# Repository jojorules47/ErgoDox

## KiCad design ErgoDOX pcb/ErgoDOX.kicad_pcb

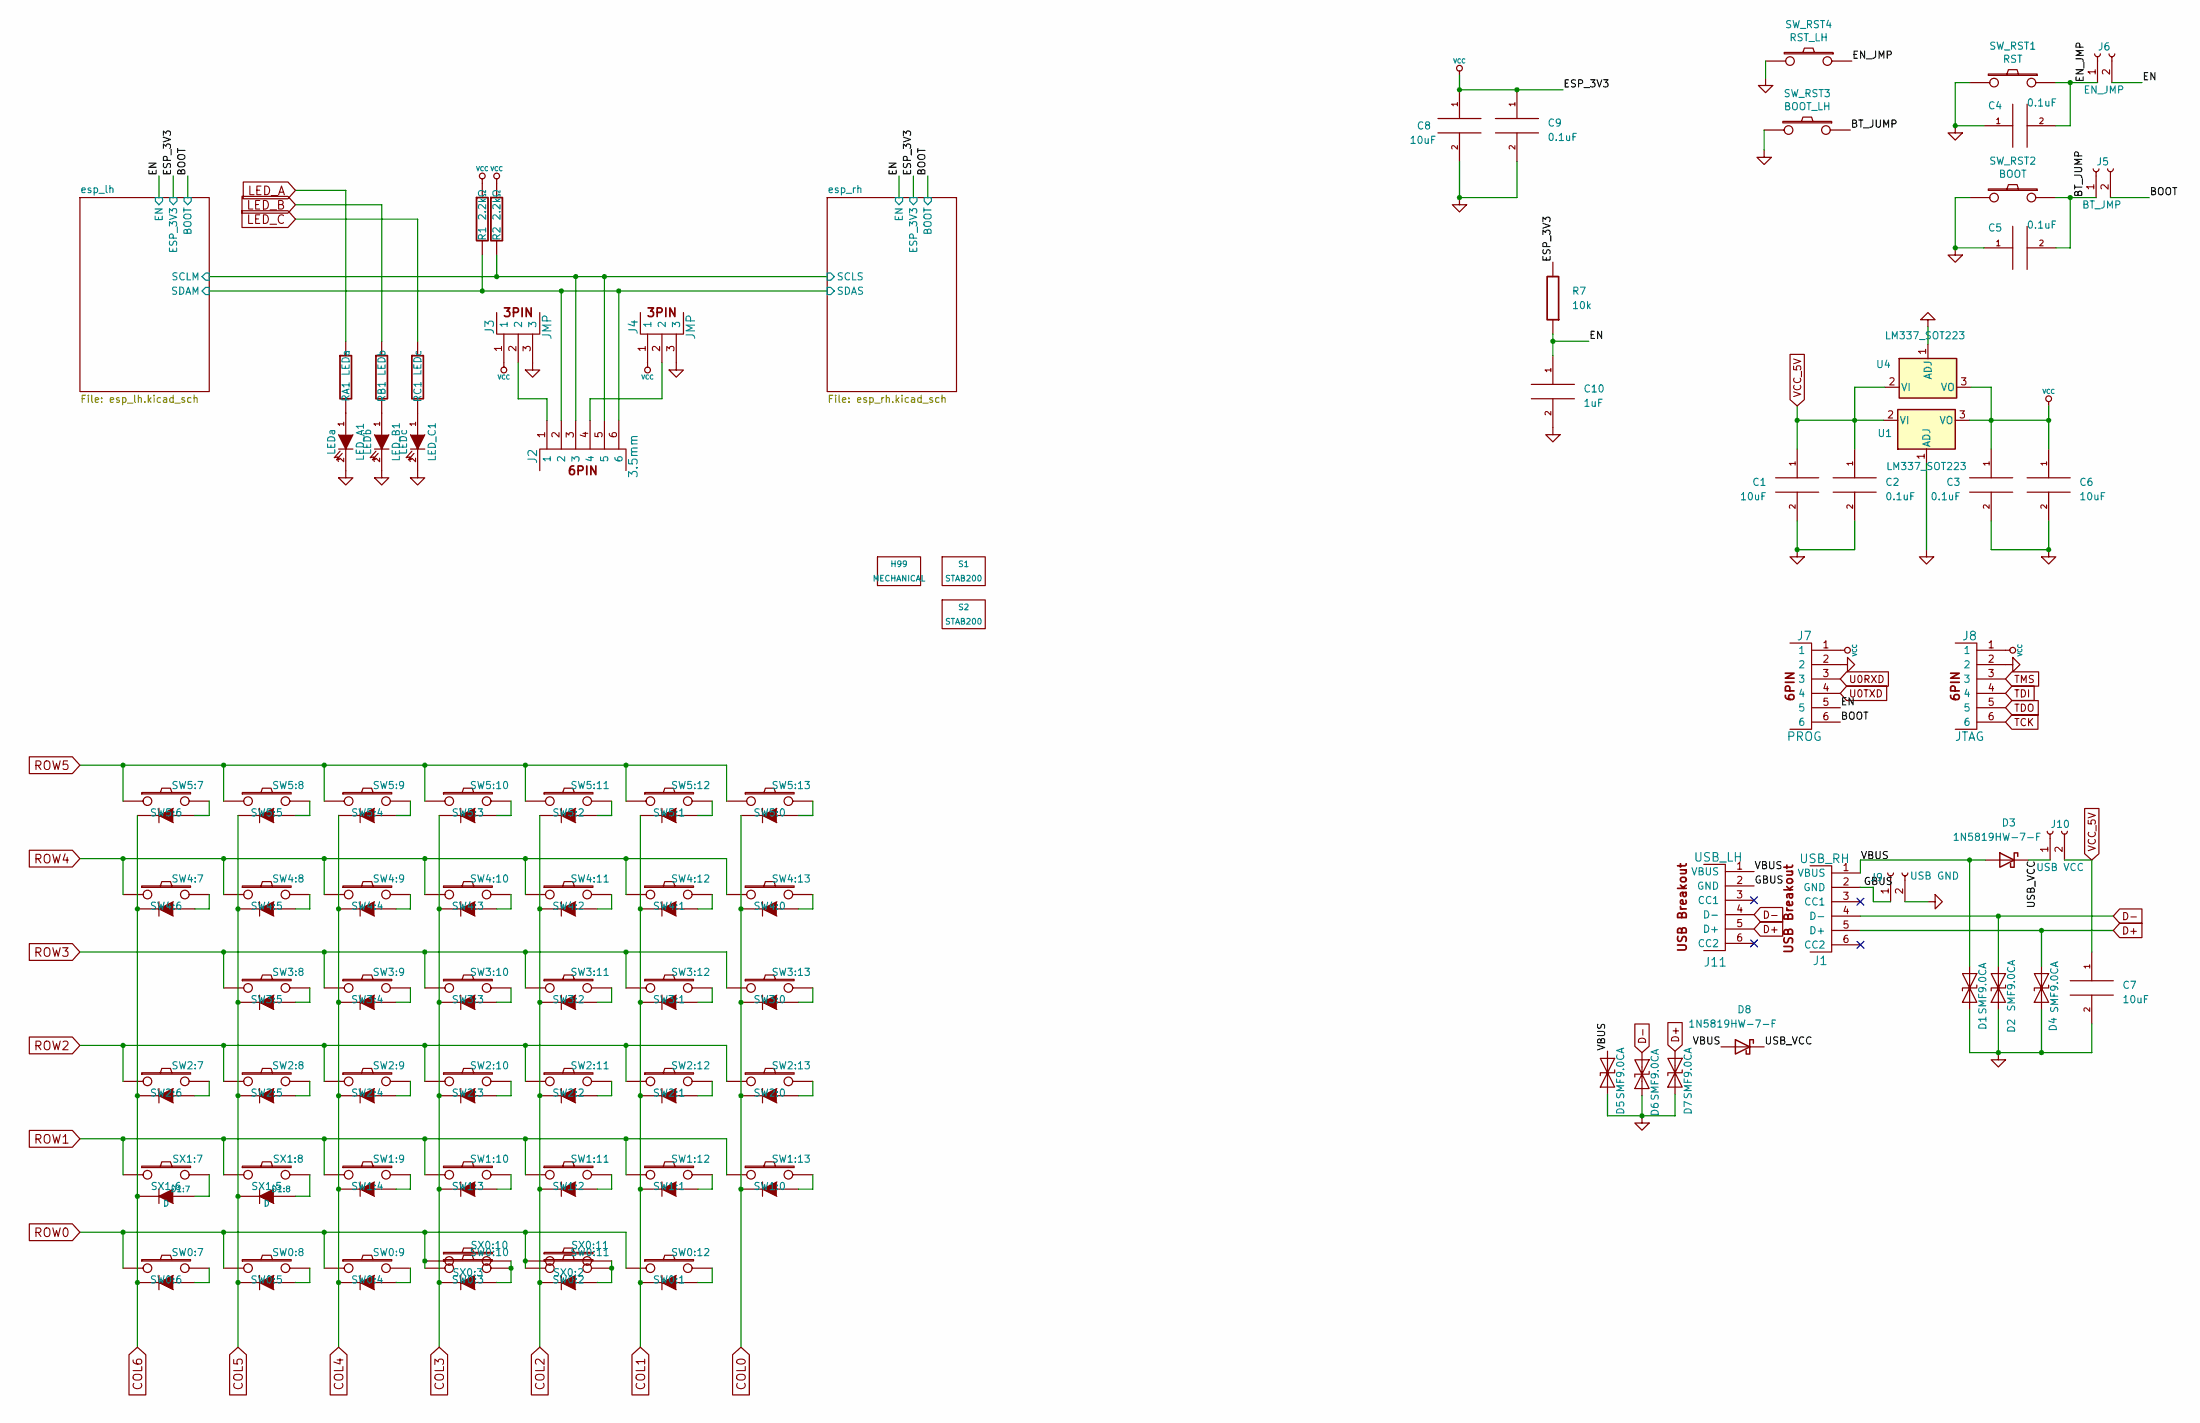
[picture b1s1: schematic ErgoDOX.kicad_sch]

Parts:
C1, C6, C7, C8: 10uF; C_Disc_D5.0mm_W2.5mm_P5.00mm
C2, C3, C4, C5, C9: 0.1uF; C_Disc_D5.0mm_W2.5mm_P5.00mm
C10: 1uF; C_Disc_D5.0mm_W2.5mm_P5.00mm
D1, D2, D4, D5, D6, D7: SMF9.0CA; D_SOD-123
D1:7, D1:8: D
D3, D8: 1N5819HW-7-F; D_SOD-123
H99: MECHANICAL
J1: USB_RH; SF USB-C Breakout
J2: 3.5mm
J3, J4: JMP
J5: BT_JMP; PinHeader_1x02_P2.54mm_Vertical
J6: EN_JMP; PinHeader_1x02_P2.54mm_Vertical
J7: PROG; PinHeader_1x06_P2.54mm_Vertical
J8: JTAG; PinHeader_1x06_P2.54mm_Vertical
J9: USB GND; PinHeader_1x02_P2.54mm_Vertical
J10: USB VCC; PinHeader_1x02_P2.54mm_Vertical
J11: USB_LH; SF USB-C Breakout
LED_A1: LEDa
LED_B1: LEDb
LED_C1: LEDc
R1, R2: 2.2kΩ; R_Axial_DIN0207_L6.3mm_D2.5mm_P7.62mm_Horizontal
R7: 10k; R_Axial_DIN0207_L6.3mm_D2.5mm_P7.62mm_Horizontal
RA1: LEDa; R_Axial_DIN0207_L6.3mm_D2.5mm_P7.62mm_Horizontal
RB1: LEDb; R_Axial_DIN0207_L6.3mm_D2.5mm_P7.62mm_Horizontal
RC1: LEDc; R_Axial_DIN0207_L6.3mm_D2.5mm_P7.62mm_Horizontal
S1, S2: STAB200
SW0:7: SW0:6
SW0:8: SW0:5
SW0:9: SW0:4
SW0:10: SW0:3
SW0:11: SW0:2
SW0:12: SW0:1
SW1:9: SW1:4
SW1:10: SW1:3
SW1:11: SW1:2
SW1:12: SW1:1
SW1:13: SW1:0
SW2:7: SW2:6
SW2:8: SW2:5
SW2:9: SW2:4
SW2:10: SW2:3
SW2:11: SW2:2
SW2:12: SW2:1
SW2:13: SW2:0
SW3:8: SW3:5
SW3:9: SW3:4
SW3:10: SW3:3
SW3:11: SW3:2
SW3:12: SW3:1
SW3:13: SW3:0
SW4:7: SW4:6
SW4:8: SW4:5
SW4:9: SW4:4
SW4:10: SW4:3
SW4:11: SW4:2
SW4:12: SW4:1
SW4:13: SW4:0
SW5:7: SW5:6
SW5:8: SW5:5
SW5:9: SW5:4
SW5:10: SW5:3
SW5:11: SW5:2
SW5:12: SW5:1
SW5:13: SW5:0
SW_RST1: RST; SW_SPST_B3U-1000P
SW_RST2: BOOT; SW_SPST_B3U-1000P
SW_RST3: BOOT_LH; SW_SPST_B3U-1000P
SW_RST4: RST_LH; SW_SPST_B3U-1000P
SX0:10: SX0:3
SX0:11: SX0:2
SX1:7: SX1:6
SX1:8: SX1:5
U1, U4: LM337_SOT223; SOT-223-3_TabPin2

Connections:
/BOOT: J5.2, J7.6; also elsewhere on the board
/BT_JUMP: C5.2, J5.1, SW_RST2.1, SW_RST3.1
/EN: C10.1, J6.2, J7.5, R7.1; also elsewhere on the board
/EN_JMP: C4.2, J6.1, SW_RST1.1, SW_RST4.1
/GBUS: J1.2 (GND), J9.1, J11.2 (GND)
/USB_VCC: D3.1 (K), D8.1 (K), J10.1
/VBUS: D1.2 (A2), D3.2 (A), D5.2 (A2), D8.2 (A), J1.1 (VBUS), J11.1 (VBUS)
COL0: SW1:13.4 (K), SW2:13.4 (K), SW3:13.4 (K), SW4:13.4 (K), SW5:13.4 (K); also elsewhere on the board
COL1: SW0:12.4 (K), SW1:12.4 (K), SW2:12.4 (K), SW3:12.4 (K), SW4:12.4 (K), SW5:12.4 (K); also elsewhere on the board
COL2: SW0:11.4 (K), SW1:11.4 (K), SW2:11.4 (K), SW3:11.4 (K), SW4:11.4 (K), SW5:11.4 (K); also elsewhere on the board
COL3: SW0:10.4 (K), SW1:10.4 (K), SW2:10.4 (K), SW3:10.4 (K), SW4:10.4 (K), SW5:10.4 (K); also elsewhere on the board
COL4: SW0:9.4 (K), SW1:9.4 (K), SW2:9.4 (K), SW3:9.4 (K), SW4:9.4 (K), SW5:9.4 (K); also elsewhere on the board
COL5: D1:8.2 (K), SW0:8.4 (K), SW2:8.4 (K), SW3:8.4 (K), SW4:8.4 (K), SW5:8.4 (K); also elsewhere on the board
COL6: D1:7.2 (K), SW0:7.4 (K), SW2:7.4 (K), SW4:7.4 (K), SW5:7.4 (K); also elsewhere on the board
D+: D4.2 (A2), D7.2 (A2), J1.5 (D+), J11.5 (D+); also elsewhere on the board
D-: D2.2 (A2), D6.2 (A2), J1.4 (D-), J11.4 (D-); also elsewhere on the board
GND: C1.2, C2.2, C3.2, C4.1, C5.1, C6.2, C7.2, C8.2, C9.2, C10.2, D1.1 (A1), D2.1 (A1), D4.1 (A1), D5.1 (A1), D6.1 (A1), D7.1 (A1), J3.3, J4.3, J7.2, J8.2, J9.2, LED_A1.2 (K), LED_B1.2 (K), LED_C1.2 (K), SW_RST1.2, SW_RST2.2, SW_RST3.2, SW_RST4.2, U1.1 (ADJ), U4.1 (ADJ); also elsewhere on the board
LED_A: RA1.1; also elsewhere on the board
LED_B: RB1.1; also elsewhere on the board
LED_C: RC1.1; also elsewhere on the board
unnamed: D1:7.1 (A), SX1:7.2
unnamed: D1:8.1 (A), SX1:8.2
unnamed: J2.4, J4.2
unnamed: J2.1, J3.2
unnamed: LED_A1.1 (A), RA1.2
unnamed: LED_B1.1 (A), RB1.2
unnamed: LED_C1.1 (A), RC1.2
unnamed: SW0:7.2, SW0:7.3 (A)
unnamed: SW0:8.2, SW0:8.3 (A)
unnamed: SW0:9.2, SW0:9.3 (A)
unnamed: SW0:10.2, SW0:10.3 (A), SX0:10.2
unnamed: SW0:11.2, SW0:11.3 (A), SX0:11.2
unnamed: SW0:12.2, SW0:12.3 (A)
unnamed: SW1:9.2, SW1:9.3 (A)
unnamed: SW1:10.2, SW1:10.3 (A)
unnamed: SW1:11.2, SW1:11.3 (A)
unnamed: SW1:12.2, SW1:12.3 (A)
unnamed: SW1:13.2, SW1:13.3 (A)
unnamed: SW2:7.2, SW2:7.3 (A)
unnamed: SW2:8.2, SW2:8.3 (A)
unnamed: SW2:9.2, SW2:9.3 (A)
unnamed: SW2:10.2, SW2:10.3 (A)
unnamed: SW2:11.2, SW2:11.3 (A)
unnamed: SW2:12.2, SW2:12.3 (A)
unnamed: SW2:13.2, SW2:13.3 (A)
unnamed: SW3:8.2, SW3:8.3 (A)
unnamed: SW3:9.2, SW3:9.3 (A)
unnamed: SW3:10.2, SW3:10.3 (A)
unnamed: SW3:11.2, SW3:11.3 (A)
unnamed: SW3:12.2, SW3:12.3 (A)
unnamed: SW3:13.2, SW3:13.3 (A)
unnamed: SW4:7.2, SW4:7.3 (A)
unnamed: SW4:8.2, SW4:8.3 (A)
unnamed: SW4:9.2, SW4:9.3 (A)
unnamed: SW4:10.2, SW4:10.3 (A)
unnamed: SW4:11.2, SW4:11.3 (A)
unnamed: SW4:12.2, SW4:12.3 (A)
unnamed: SW4:13.2, SW4:13.3 (A)
unnamed: SW5:7.2, SW5:7.3 (A)
unnamed: SW5:8.2, SW5:8.3 (A)
unnamed: SW5:9.2, SW5:9.3 (A)
unnamed: SW5:10.2, SW5:10.3 (A)
unnamed: SW5:11.2, SW5:11.3 (A)
unnamed: SW5:12.2, SW5:12.3 (A)
unnamed: SW5:13.2, SW5:13.3 (A)
ROW0: SW0:7.1, SW0:8.1, SW0:9.1, SW0:10.1, SW0:11.1, SW0:12.1, SX0:10.1, SX0:11.1; also elsewhere on the board
ROW1: SW1:9.1, SW1:10.1, SW1:11.1, SW1:12.1, SW1:13.1, SX1:7.1, SX1:8.1; also elsewhere on the board
ROW2: SW2:7.1, SW2:8.1, SW2:9.1, SW2:10.1, SW2:11.1, SW2:12.1, SW2:13.1; also elsewhere on the board
ROW3: SW3:8.1, SW3:9.1, SW3:10.1, SW3:11.1, SW3:12.1, SW3:13.1; also elsewhere on the board
ROW4: SW4:7.1, SW4:8.1, SW4:9.1, SW4:10.1, SW4:11.1, SW4:12.1, SW4:13.1; also elsewhere on the board
ROW5: SW5:7.1, SW5:8.1, SW5:9.1, SW5:10.1, SW5:11.1, SW5:12.1, SW5:13.1; also elsewhere on the board
TCK: J8.6; also elsewhere on the board
TDI: J8.4; also elsewhere on the board
TDO: J8.5; also elsewhere on the board
TMS: J8.3; also elsewhere on the board
U0RXD: J7.3; also elsewhere on the board
U0TXD: J7.4; also elsewhere on the board
VCC: C3.1, C6.1, C8.1, C9.1, J3.1, J4.1, J7.1, J8.1, R1.1, R2.1, R7.2, U1.3 (VO), U4.3 (VO); also elsewhere on the board
VCC_5V: C1.1, C2.1, C7.1, J10.2, U1.2 (VI), U4.2 (VI)

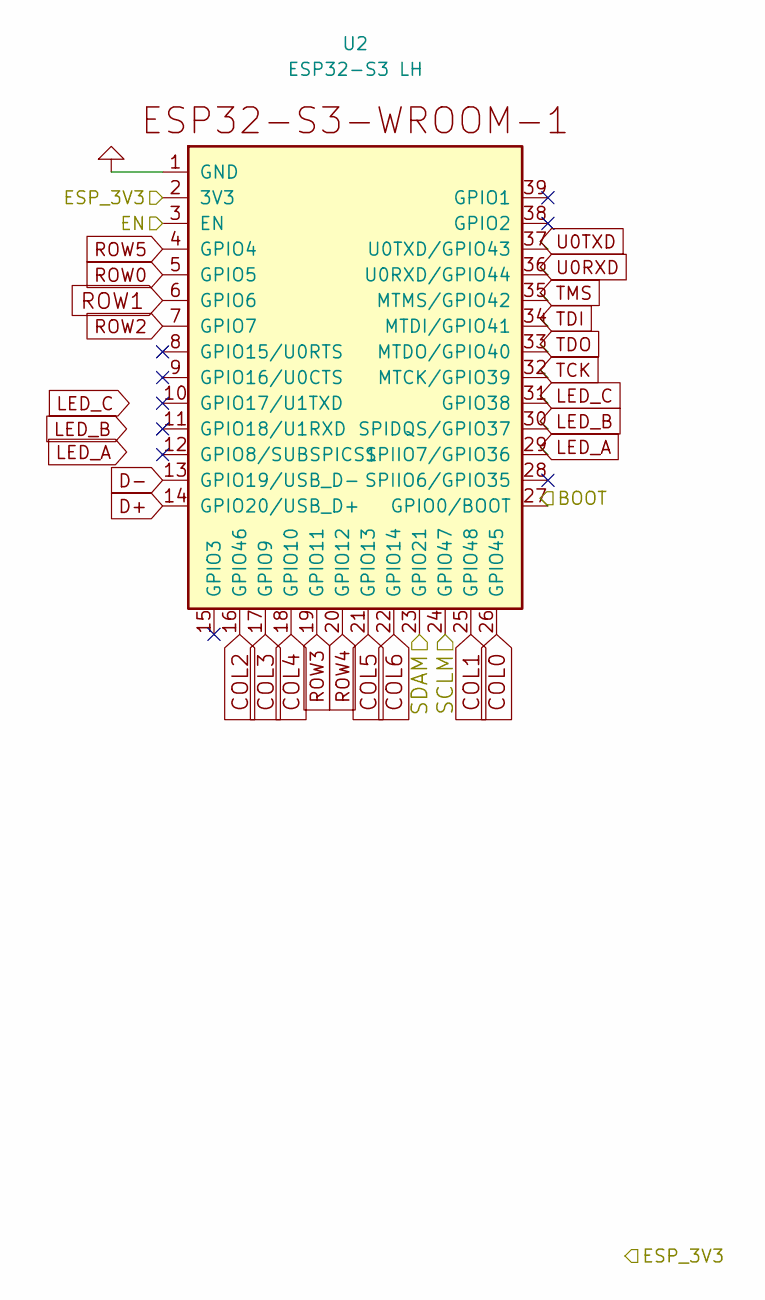
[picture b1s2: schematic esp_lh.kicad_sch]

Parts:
U2: ESP32-S3 LH; ESP32-S3-WROOM-1

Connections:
/BOOT: U2.27 (GPIO0/BOOT); also elsewhere on the board
/EN: U2.3 (EN); also elsewhere on the board
COL0: U2.26 (GPIO45); also elsewhere on the board
COL1: U2.25 (GPIO48); also elsewhere on the board
COL2: U2.16 (GPIO46); also elsewhere on the board
COL3: U2.17 (GPIO9); also elsewhere on the board
COL4: U2.18 (GPIO10); also elsewhere on the board
COL5: U2.21 (GPIO13); also elsewhere on the board
COL6: U2.22 (GPIO14); also elsewhere on the board
D+: U2.14 (GPIO20/USB_D+); also elsewhere on the board
D-: U2.13 (GPIO19/USB_D-); also elsewhere on the board
GND: U2.1 (GND); also elsewhere on the board
LED_A: U2.29 (SPIIO7/GPIO36); also elsewhere on the board
LED_B: U2.30 (SPIDQS/GPIO37); also elsewhere on the board
LED_C: U2.31 (GPIO38); also elsewhere on the board
ROW0: U2.5 (GPIO5); also elsewhere on the board
ROW1: U2.6 (GPIO6); also elsewhere on the board
ROW2: U2.7 (GPIO7); also elsewhere on the board
ROW3: U2.19 (GPIO11); also elsewhere on the board
ROW4: U2.20 (GPIO12); also elsewhere on the board
ROW5: U2.4 (GPIO4); also elsewhere on the board
TCK: U2.32 (MTCK/GPIO39); also elsewhere on the board
TDI: U2.34 (MTDI/GPIO41); also elsewhere on the board
TDO: U2.33 (MTDO/GPIO40); also elsewhere on the board
TMS: U2.35 (MTMS/GPIO42); also elsewhere on the board
U0RXD: U2.36 (U0RXD/GPIO44); also elsewhere on the board
U0TXD: U2.37 (U0TXD/GPIO43); also elsewhere on the board
VCC: U2.2 (3V3); also elsewhere on the board

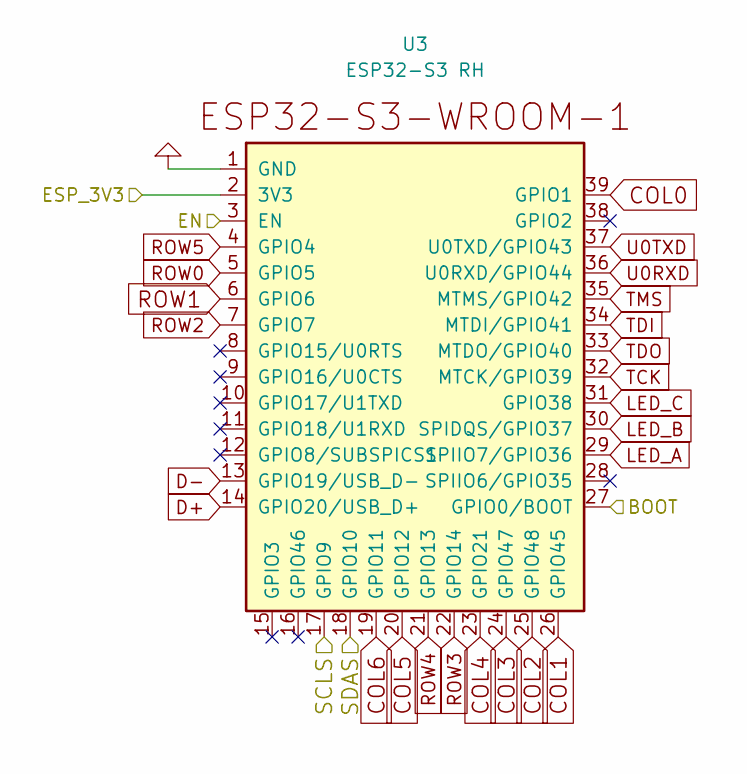
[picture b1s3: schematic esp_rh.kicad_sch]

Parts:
U3: ESP32-S3 RH; ESP32-S3-WROOM-1

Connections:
/BOOT: U3.27 (GPIO0/BOOT); also elsewhere on the board
/EN: U3.3 (EN); also elsewhere on the board
COL0: U3.39 (GPIO1); also elsewhere on the board
COL1: U3.26 (GPIO45); also elsewhere on the board
COL2: U3.25 (GPIO48); also elsewhere on the board
COL3: U3.24 (GPIO47); also elsewhere on the board
COL4: U3.23 (GPIO21); also elsewhere on the board
COL5: U3.20 (GPIO12); also elsewhere on the board
COL6: U3.19 (GPIO11); also elsewhere on the board
D+: U3.14 (GPIO20/USB_D+); also elsewhere on the board
D-: U3.13 (GPIO19/USB_D-); also elsewhere on the board
GND: U3.1 (GND); also elsewhere on the board
LED_A: U3.29 (SPIIO7/GPIO36); also elsewhere on the board
LED_B: U3.30 (SPIDQS/GPIO37); also elsewhere on the board
LED_C: U3.31 (GPIO38); also elsewhere on the board
ROW0: U3.5 (GPIO5); also elsewhere on the board
ROW1: U3.6 (GPIO6); also elsewhere on the board
ROW2: U3.7 (GPIO7); also elsewhere on the board
ROW3: U3.22 (GPIO14); also elsewhere on the board
ROW4: U3.21 (GPIO13); also elsewhere on the board
ROW5: U3.4 (GPIO4); also elsewhere on the board
TCK: U3.32 (MTCK/GPIO39); also elsewhere on the board
TDI: U3.34 (MTDI/GPIO41); also elsewhere on the board
TDO: U3.33 (MTDO/GPIO40); also elsewhere on the board
TMS: U3.35 (MTMS/GPIO42); also elsewhere on the board
U0RXD: U3.36 (U0RXD/GPIO44); also elsewhere on the board
U0TXD: U3.37 (U0TXD/GPIO43); also elsewhere on the board
VCC: U3.2 (3V3); also elsewhere on the board

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
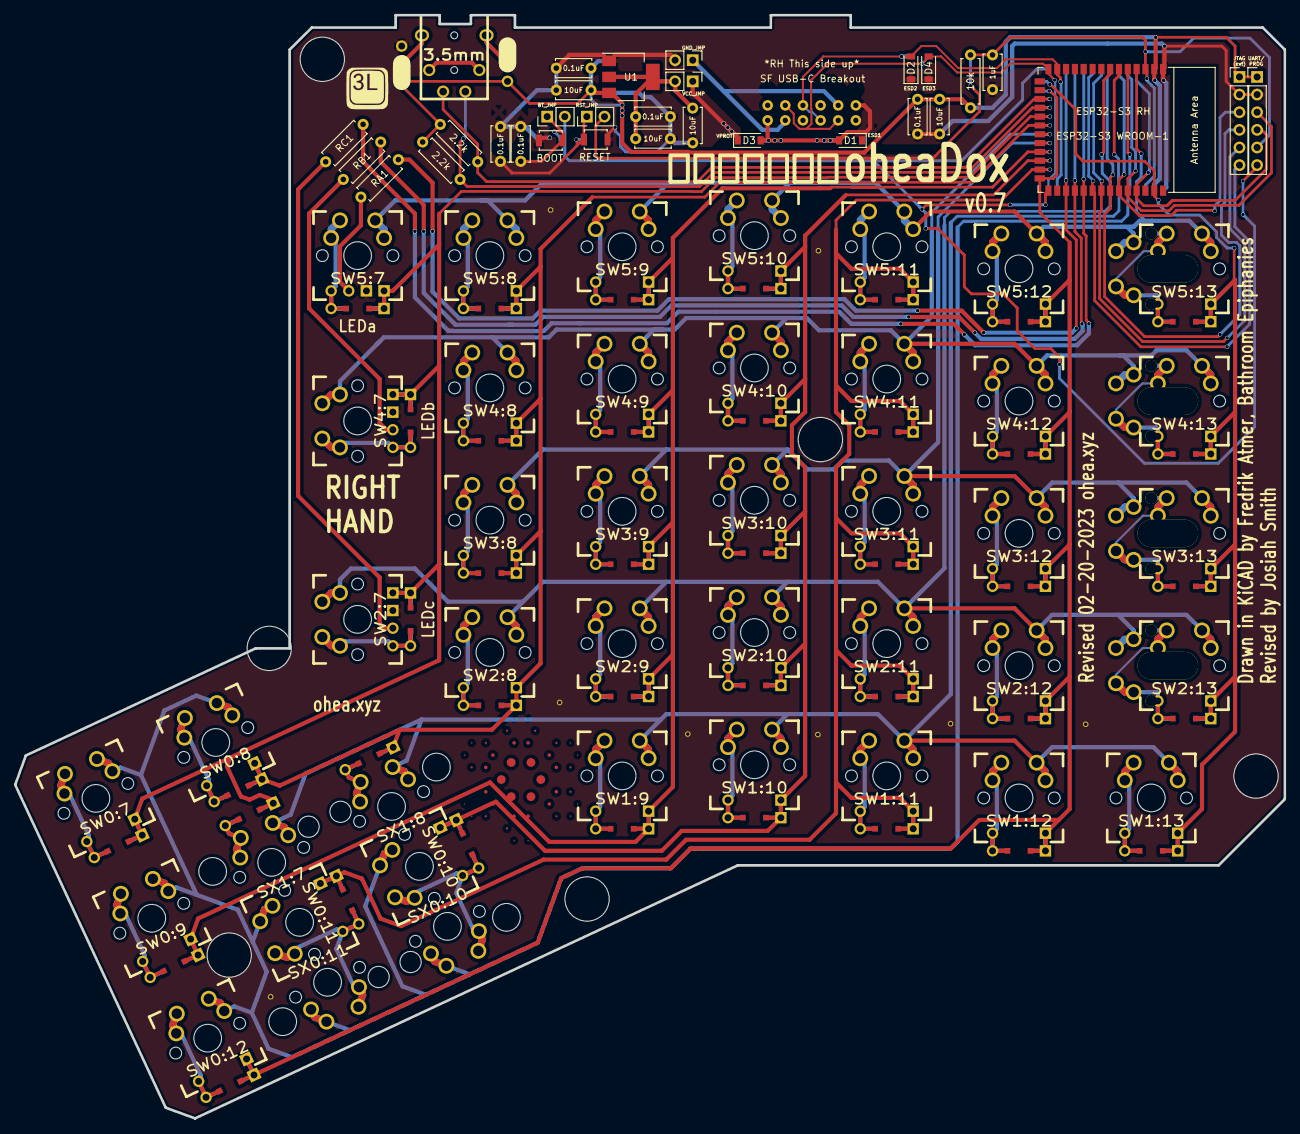
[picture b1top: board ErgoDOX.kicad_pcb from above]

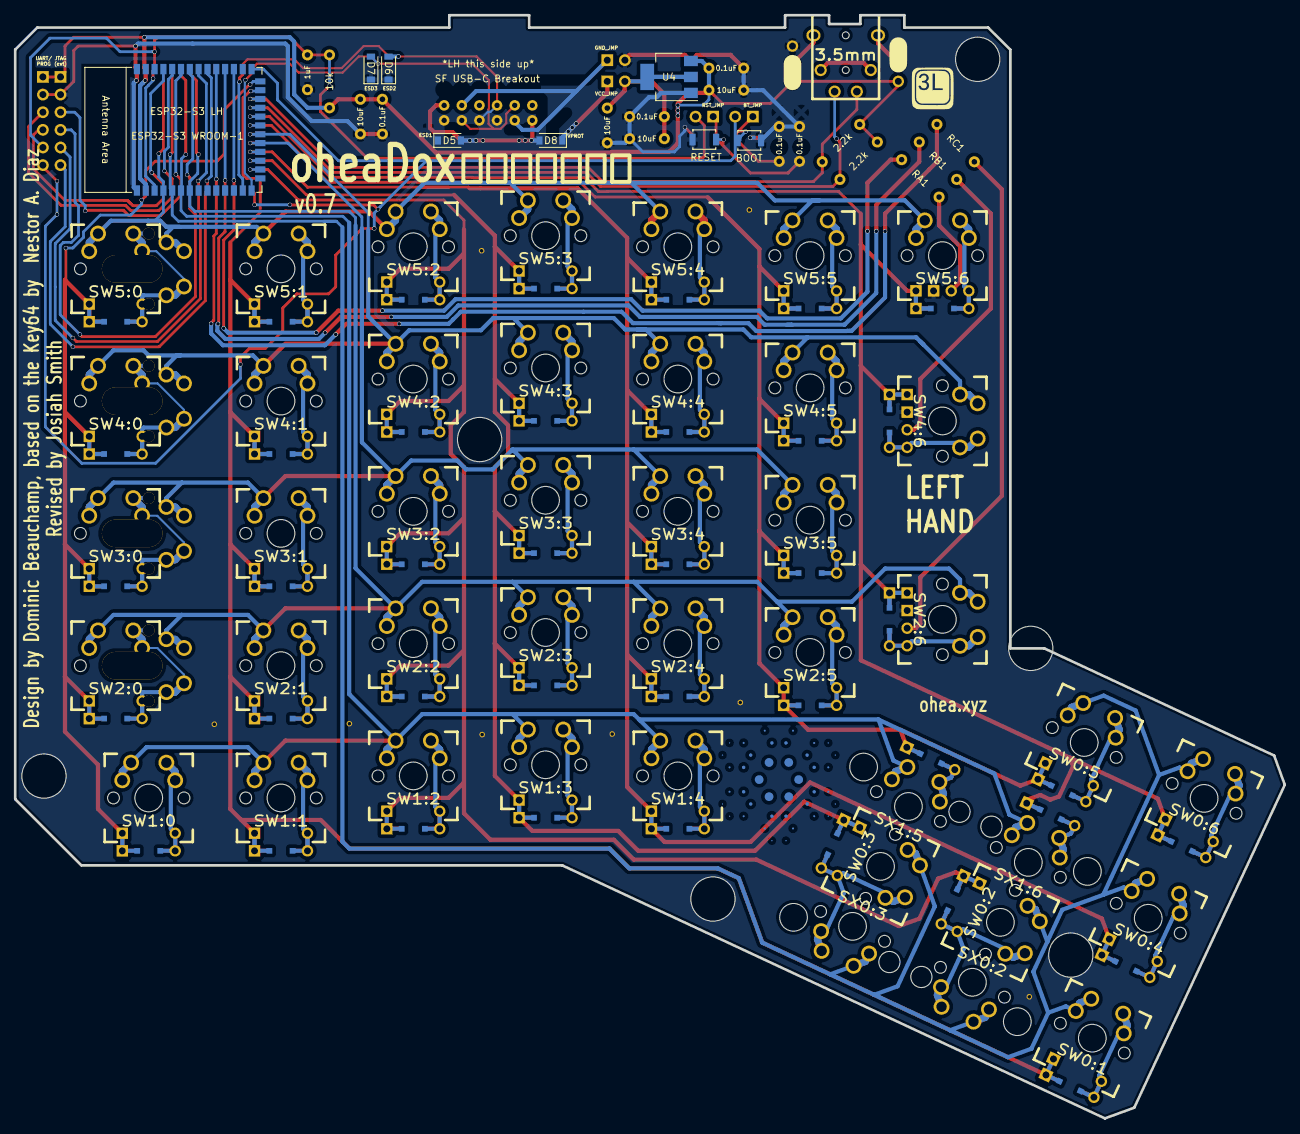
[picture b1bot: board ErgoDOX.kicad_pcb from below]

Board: 2 copper layers, 182.8 x 158.9 mm, 102 parts (11 on the bottom side), 82 nets.

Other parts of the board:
STAR_1: STAR_FRONT; STAR
STAR_2: STAR_BACK; STAR
STITCHING_VIA: STITCHING_VIA
STITCHING_VIA#2, STITCHING_VIA#3, STITCHING_VIA#4, STITCHING_VIA#5, STITCHING_VIA#6, STITCHING_VIA#7, STITCHING_VIA#8: STITCHING_VIA

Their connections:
COL3: STAR_1.1, STAR_1.2; also elsewhere on the board
COL4: STAR_1.0, STAR_1.1, STAR_1.3, STAR_1.4; also elsewhere on the board
GND: STITCHING_VIA.GND, STITCHING_VIA#2.GND, STITCHING_VIA#3.GND, STITCHING_VIA#4.GND, STITCHING_VIA#5.GND, STITCHING_VIA#6.GND, STITCHING_VIA#7.GND, STITCHING_VIA#8.GND; also elsewhere on the board
ROW1: STAR_2.5, STAR_2.6; also elsewhere on the board

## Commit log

2023-01-30 Remap pins from Teensy2,0 to TinyS3
2023-02-10 Add two-handed ESP32-S3 boards
2023-02-13 Create preliminary layout
2023-02-19 Place components in more final layout
2023-02-20 First route of board
2023-02-21 Add back components, silk screen
2023-02-22 Add silkscreen notes and logo
2023-02-22 Remove unused silkscreen
